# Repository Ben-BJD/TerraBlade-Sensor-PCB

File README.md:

# 🌱 TerraBlade Sensor - Hardware PCB

---

**TerraBlade** is a professional-grade, ultra-low-power capacitive soil moisture sensor designed around the Seeed Studio XIAO ESP32-C3. 

This repository contains the complete KiCad 9 hardware design files, manufacturing plots, and mechanical Inkscape references for the PCB assembly. This board is designed using a **"PCBA-Driven"** workflow, meaning the electronics were engineered first, acting as the structural core for a modular 3D-printed enclosure.

Created by [BJD Solutions](https://bj-dehaan-solutions.com.au/).

---

## Key Engineering Features

*   **True Digital Capacitive Sensing:** Ditching the noisy, drifty analog peak-detectors of standard cheap soil sensors. The FR4 PCB blade acts as the timing capacitor for an industrial-grade **TLC555IDR** oscillator. It outputs a raw, clean frequency directly to the ESP32's hardware Pulse Counter (PCNT) for flawless, high-resolution moisture data.
*   **Zero-Leakage "Parasitic" Power:** The 555 timer is powered directly by an ESP32 GPIO pin. The ESP32 wakes up, powers the sensor, takes a reading, and kills the power before going back to sleep. Sensor quiescent current: **0.0µA**.
*   **Panelized 3-in-1 Design:** The **Radio PCB**, **Power Hat**, and **Sensor Blade** are all designed to be manufactured on a single 100x100mm panel connected by mouse-bites to save on fabrication costs.
*   **Mortise & Tenon Assembly:** The Sensor Blade features a custom "tenon" tab that slots perfectly into the main Radio PCB and is soldered directly at a 90-degree angle, requiring zero wires.
*   **Pogo-Pin Power Hat:** Handles the mechanical shear force of a plunging outdoor sensor by using through-hole Pogo Pins (spring-loaded contacts) rather than weak SMD conical springs.
*   **Low-Voltage Optimized:** Features an ultra-efficient 573nm Yellow-Green LED that requires only ~2.0V to light up. It will reliably flash in "Config Mode" even when the 3x AA batteries are nearly dead. Includes a precision 1% 220kΩ voltage divider for highly accurate battery monitoring.

---

## 📂 Repository Structure

*   Full KiCad 9 project files (`.kicad_pro`, `.kicad_sch`, `.kicad_pcb`).
*   Ready-to-order plot files, drill files, and the solder paste stencil map.
*   High-resolution PDF exports of the schematic and PCB layers.
*   Original Inkscape (`.svg`) files used to perfectly calculate the complex `Edge.Cuts` curves, alignment notches, and Mortise & Tenon joints.

---

## 🛠️ Assembly & Manufacturing Notes

If you are ordering these boards from a fabricator please note the following:

1.  **Thickness:** Order in standard **1.6mm FR4**. The Mortise and Tenon slot on the Radio PCB is routed to exactly 1.7mm to provide a perfect slip-fit for 1.6mm thick material.
2.  **Solder Mask is Mandatory:** Do NOT expose the copper on the Sensor Blade. The blade relies on the green Solder Mask to act as a waterproof dielectric barrier. Exposing the copper to wet soil will cause rapid galvanic corrosion and destroy the sensor.
3.  **Keyway Notches:** The Radio PCB and Power Hat feature an 8-o'clock alignment notch. This is an asymmetrical keyway designed to interface with a matching rail in the future 3D-printed enclosure, preventing the board from twisting or being inserted backward.
4.  **Solder Paste Stencil:** The `F.Paste` layer has been custom-tailored to remove paste from the structural Mortise & Tenon joints, allowing for clean, manual fillet soldering without bridging.

---

## 🛒 BOM Highlights (LCSC)

The full [BOM](BOM.csv) is included and can be generated from the KiCad schematic, here are the critical components used in this design:

*   **Microcontroller:** Seeed Studio XIAO ESP32-C3
*   **Timer IC:** TLC555IDR (Industrial Temp Range: -40°C to 85°C) - *LCSC: C6987*
*   **Pogo Pins (Power Contacts):** CHIN-BAN PG1000-01-010P (1A Through-Hole) - *LCSC: C49451494*
*   **Config LED:** TUOZHAN 0805 Yellow-Green 573nm (1.8V-2.4V) - *LCSC: C688885*
*   **Tactile Switch:** TS-1187A-B-A-B (4-pin SMD) - *LCSC: C318884*

---

## 📄 License

This hardware design is open-source. Feel free to build it, mod it, and plant it! 
Designed by [BJD Solutions](https://bj-dehaan-solutions.com.au/).

---

## Schematic:

[PDF Version](TerraBlade-Sensor-Schematic.pdf)

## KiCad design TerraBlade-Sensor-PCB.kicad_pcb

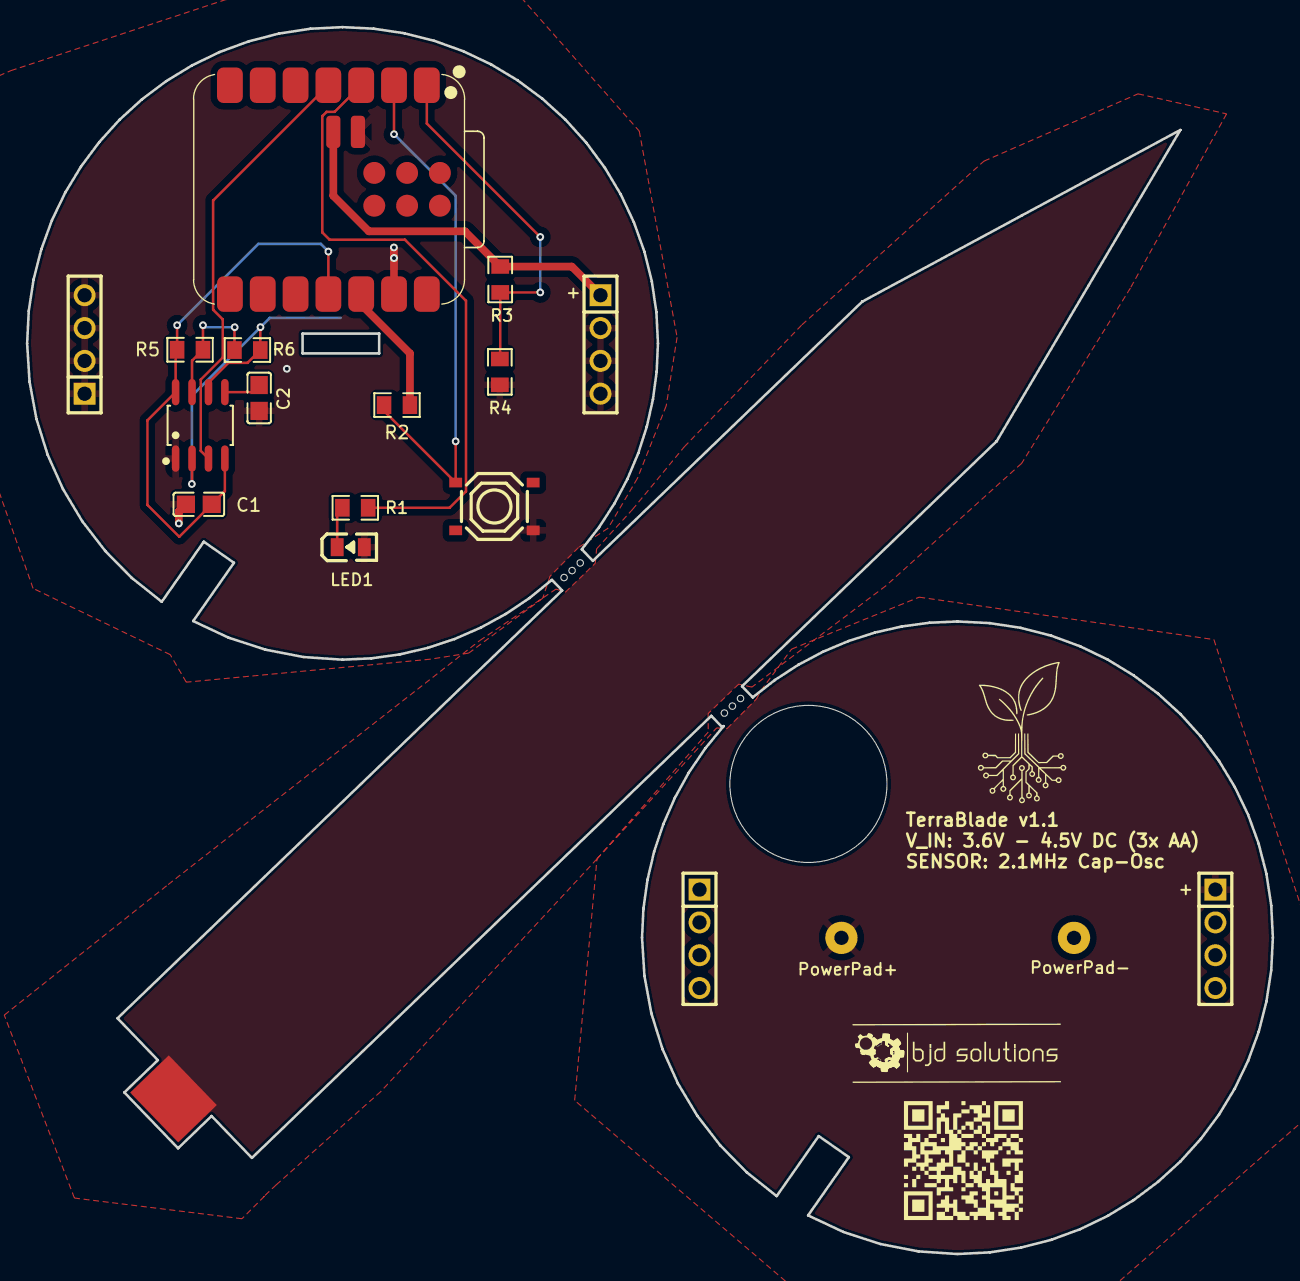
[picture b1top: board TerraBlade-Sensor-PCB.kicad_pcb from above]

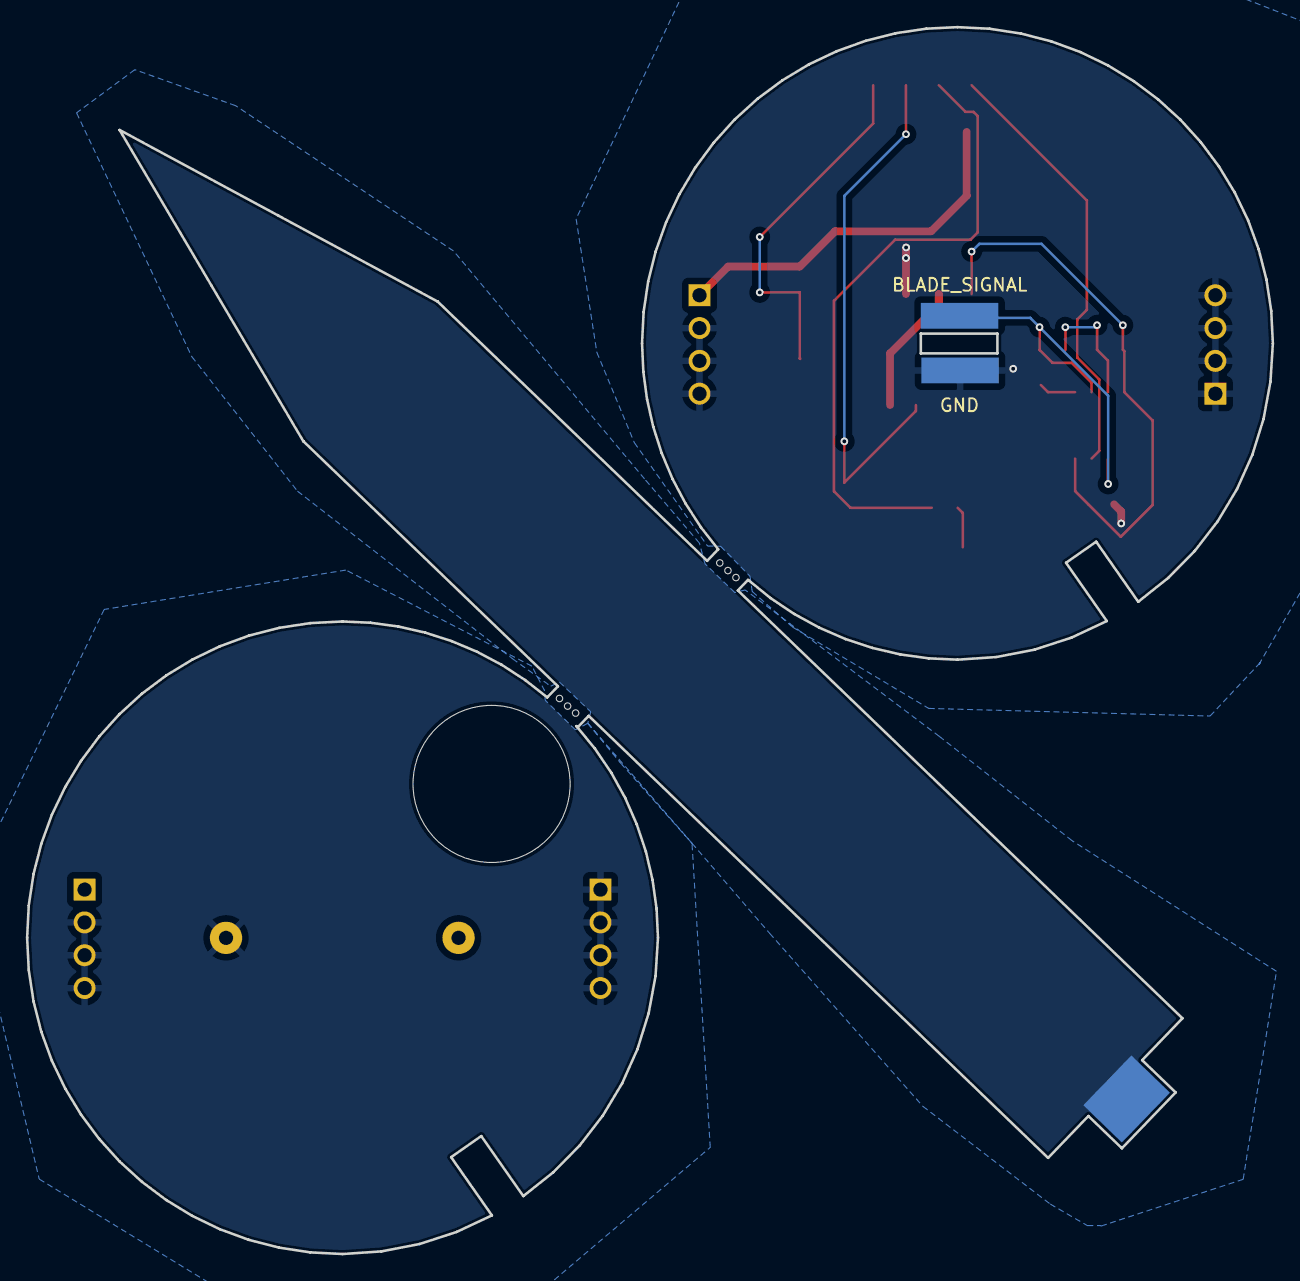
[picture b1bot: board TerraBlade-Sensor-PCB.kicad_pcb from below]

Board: 2 copper layers, 96.4 x 95.0 mm, 22 parts (3 on the bottom side), 14 nets.

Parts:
+: PZ254V-11-04P_C2691448; HDR-TH_4P-P2.54-V-M
+#2: 2.54-1*4P母; HDR-TH_4P-P2.54-V-F
BLADE_SIGNAL: BladePad; BladePad_SMD
C1: 0.1uF 50V 10%; C0805
C2: 10nF; C0805
CN3: PowerPad+; TESTPOINT-SMD_BD2.0-D1.0-Custom
CN4: PowerPad-; TESTPOINT-SMD_BD2.0-D1.0-Custom
GND: BladePad; BladePad_SMD
H2: 2.54-1*4P母; HDR-TH_4P-P2.54-V-F
H6: PZ254V-11-04P_C2691448; HDR-TH_4P-P2.54-V-M
LED1: TZ-P2-0805YGTCS2-0.8T; LED0805-R-RD_GREEN
PAD5, PAD6: BladePad; BladePad_SMD
R1: 1kΩ; R0805
R2, R5: 10K 1%; R0805
R3, R4: 220kΩ; R0805
R6: 100kΩ; R0805
SW1: TS-1187A-B-A-B; SW-SMD_4P-L5.1-W5.1-P3.70-LS6.5-TL_H1.5
U1: XIAO-ESP32-C3-SMD
U2: 2.1MHz; SOIC-8_L4.9-W3.9-P1.27-LS6.0-BL

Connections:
+3.3V: R2.2, U1.12 (3V3)
BAT+: +#2.1, R3.1, U1.32 (BAT)
BLADE_SIGNAL: BLADE_SIGNAL.1, R6.1, U2.2 (TRIG), U2.6 (THRES)
ESP32_D2: R1.1, U1.3 (GPIO4_A2_D2)
ESP32_D3: U1.4 (GPIO5_A3_D3), U2.3 (OUT)
ESP32_D10: C1.1, R5.2, U1.11 (GPIO10_D10_MOSI), U2.4 (RESET), U2.8 (VDD)
GND: +#2.2, +#2.3, +#2.4, C1.2, C2.2, GND.1, H2.1, H2.2, H2.3, H2.4, LED1.1 (A), R4.1, SW1.4 (D), U1.13 (GND), U1.33 (GND), U2.1 (GND)
unnamed: LED1.2 (K), R1.2
unnamed: R2.1, SW1.1 (A), U1.2 (GPIO3_A1_D1)
unnamed: R3.2, R4.2, U1.1 (GPIO2_A0_D0)
unnamed: C2.1, U2.5 (CONT)
unnamed: R5.1, R6.2, U2.7 (DISCH)
POWER_PAD_+: +.1, CN3.1
POWER_PAD_-: +.2, +.3, +.4, CN4.1, H6.1, H6.2, H6.3, H6.4

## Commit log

2026-04-11 PCB Design
2026-04-12 PCB Layout
2026-05-10 Remap Digital Pins (Don't use strapping pins) / Increase size of the mortise tenon slot
2026-05-10 Silk Screen changes
2026-05-25 Update README with project images and article links
2026-05-25 Update README to reorder tutorial and article links
